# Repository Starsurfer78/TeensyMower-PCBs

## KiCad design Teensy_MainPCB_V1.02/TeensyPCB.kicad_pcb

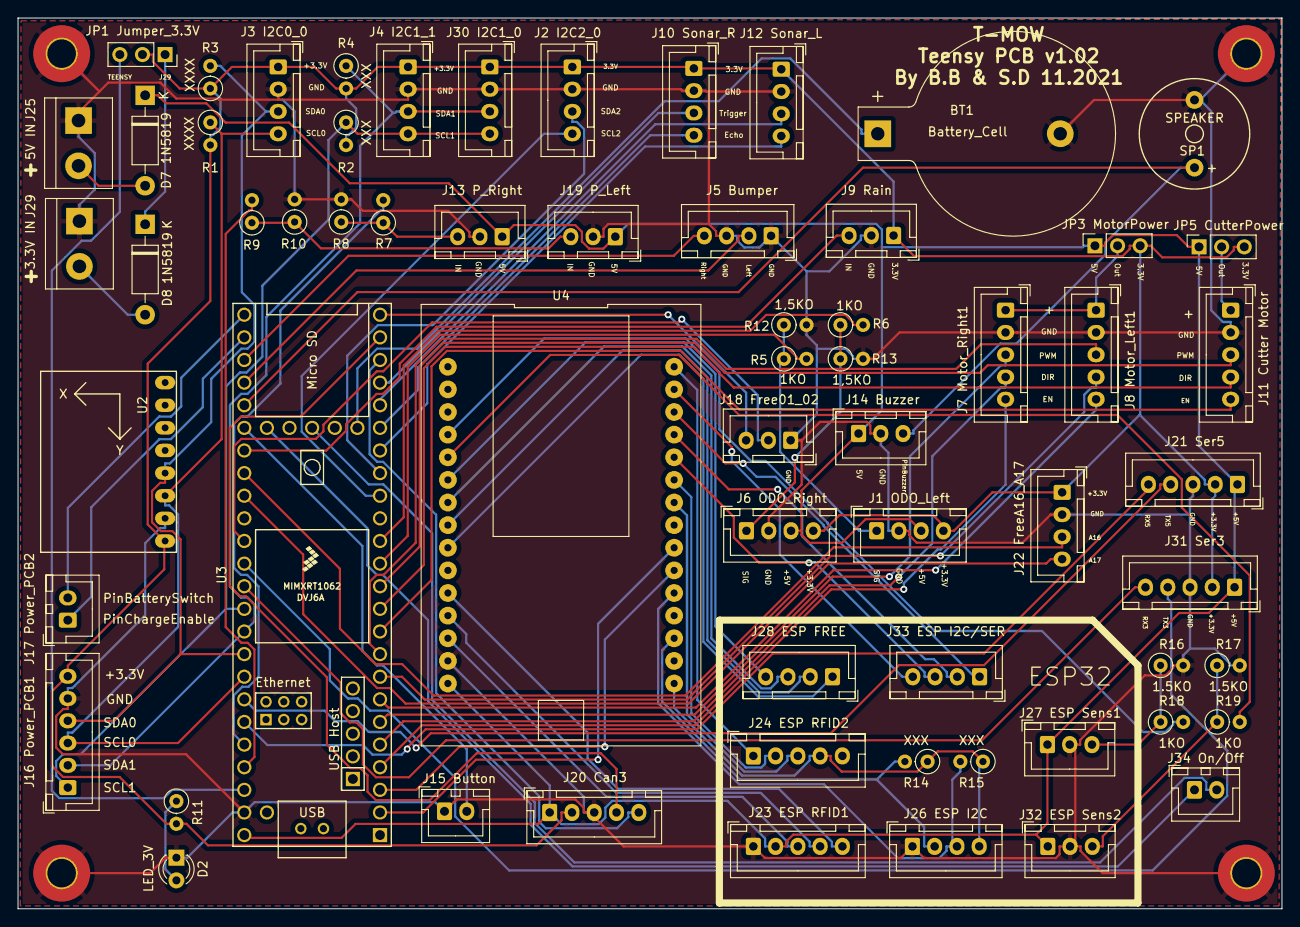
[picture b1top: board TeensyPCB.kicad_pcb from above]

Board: 2 copper layers, 141.9 x 100.0 mm, 68 parts (0 on the bottom side), 80 nets.

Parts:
BT1: Battery_Cell; BatteryHolder_Keystone_103_1x20mm
D2: LED_3V; LED_D3.0mm
D7, D8: 1N5819; D_DO-41_SOD81_P10.16mm_Horizontal
H1, H2, H3, H4: MountingHole_Pad; MountingHole_3.2mm_M3_Pad_TopBottom
J1 ODO_Left: ODO_Left; JST_XH_B4B-XH-A_1x04_P2.50mm_Vertical
J2 I2C2_0: I2C2_0; JST_XH_B4B-XH-A_1x04_P2.50mm_Vertical
J3 I2C0_0: I2C0_0; JST_XH_B4B-XH-A_1x04_P2.50mm_Vertical
J4 I2C1_1: I2C1_1; JST_XH_B4B-XH-A_1x04_P2.50mm_Vertical
J5 Bumper: Bumper; JST_XH_B4B-XH-A_1x04_P2.50mm_Vertical
J6 ODO_Right: ODO_Right; JST_XH_B4B-XH-A_1x04_P2.50mm_Vertical
J7 Motor_Right1: Motor_Right1; JST_XH_B5B-XH-A_1x05_P2.50mm_Vertical
J8 Motor_Left1: Motor_Left1; JST_XH_B5B-XH-A_1x05_P2.50mm_Vertical
J9 Rain: Rain; JST_XH_B3B-XH-A_1x03_P2.50mm_Vertical
J10 Sonar_R: Sonar_R; JST_XH_B4B-XH-A_1x04_P2.50mm_Vertical
J11 Cutter Motor: Cutter; JST_XH_B5B-XH-A_1x05_P2.50mm_Vertical
J12 Sonar_L: Sonar_L; JST_XH_B4B-XH-A_1x04_P2.50mm_Vertical
J13 P_Right: P_Right; JST_XH_B3B-XH-A_1x03_P2.50mm_Vertical
J14 Buzzer: Buzzer; JST_XH_B3B-XH-A_1x03_P2.50mm_Vertical
J15 Button: Button; JST_XH_B2B-XH-A_1x02_P2.50mm_Vertical
J16 Power_PCB1: Power_PCB1; JST_XH_B6B-XH-A_1x06_P2.50mm_Vertical
J17 Power_PCB2: Power_PCB2; JST_XH_B2B-XH-A_1x02_P2.50mm_Vertical
J18 Free01_02: Free01_02; JST_XH_B3B-XH-A_1x03_P2.50mm_Vertical
J19 P_Left: P_Left; JST_XH_B3B-XH-A_1x03_P2.50mm_Vertical
J20 Can3: Can3; JST_XH_B5B-XH-A_1x05_P2.50mm_Vertical
J21 Ser5: Ser5; JST_XH_B5B-XH-A_1x05_P2.50mm_Vertical
J22 FreeA16_A17: FreeA16_A17; JST_XH_B4B-XH-A_1x04_P2.50mm_Vertical
J23 ESP RFID1: ESP RFID1; JST_XH_B5B-XH-A_1x05_P2.50mm_Vertical
J24 ESP RFID2: ESP RFID2; JST_XH_B5B-XH-A_1x05_P2.50mm_Vertical
J25: 5V IN; TerminalBlock_bornier-2_P5.08mm
J26 ESP I2C: ESP32 I2C; JST_XH_B4B-XH-A_1x04_P2.50mm_Vertical
J27 ESP Sens1: ESP32 Sens1; JST_XH_B3B-XH-A_1x03_P2.50mm_Vertical
J28 ESP FREE: ESP32 FREE; JST_XH_B4B-XH-A_1x04_P2.50mm_Vertical
J29: 3.3V IN; TerminalBlock_bornier-2_P5.08mm
J30 I2C1_0: I2C1_0; JST_XH_B4B-XH-A_1x04_P2.50mm_Vertical
J31 Ser3: Ser3; JST_XH_B5B-XH-A_1x05_P2.50mm_Vertical
J32 ESP Sens2: ESP32 Sens2; JST_XH_B3B-XH-A_1x03_P2.50mm_Vertical
J33 ESP I2C/SER: ESP32 I2C/SER; JST_XH_B4B-XH-A_1x04_P2.50mm_Vertical
J34 On/Off: Teensy On/Off; JST_XH_B2B-XH-A_1x02_P2.50mm_Vertical
JP1 Jumper_3.3V: Jumper_3.3V; PinSocket_1x03_P2.54mm_Vertical
JP3 MotorPower: MotorPower; PinSocket_1x03_P2.54mm_Vertical
JP5 CutterPower: CutterPower; PinSocket_1x03_P2.54mm_Vertical
R1, R3: XXXX; R_Axial_DIN0207_L6.3mm_D2.5mm_P2.54mm_Vertical
R2, R4, R14, R15: XXX; R_Axial_DIN0207_L6.3mm_D2.5mm_P2.54mm_Vertical
R5, R6, R7, R9, R18, R19: 1KO; R_Axial_DIN0207_L6.3mm_D2.5mm_P2.54mm_Vertical
R8, R10, R16, R17: 1.5KO; R_Axial_DIN0207_L6.3mm_D2.5mm_P2.54mm_Vertical
R11: 100; R_Axial_DIN0207_L6.3mm_D2.5mm_P2.54mm_Vertical
R12, R13: 1,5KO; R_Axial_DIN0207_L6.3mm_D2.5mm_P2.54mm_Vertical
SP1: SPEAKER; Buzzer_12x9.5RM7.6
U2: GY-521
U3: Teensy4.1; Teensy41
U4: ESP32-DEVKIT-V1

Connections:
+3V3: J1 ODO_Left.4, J2 I2C2_0.1, J3 I2C0_0.1, J4 I2C1_1.1, J6 ODO_Right.4, J9 Rain.1, J10 Sonar_R.1, J12 Sonar_L.1, J16 Power_PCB1.6, J20 Can3.2, J21 Ser5.2, J22 FreeA16_A17.1, J30 I2C1_0.1, J31 Ser3.2, JP1 Jumper_3.3V.2, JP3 MotorPower.3, JP5 CutterPower.3, R1.2, R2.2, R3.1, R4.2, R11.2, U2.1
+5V: D7.1, J1 ODO_Left.3, J6 ODO_Right.3, J13 P_Right.1, J14 Buzzer.1, J19 P_Left.1, J20 Can3.1, J21 Ser5.1, J23 ESP RFID1.2, J27 ESP Sens1.1, J31 Ser3.1, J32 ESP Sens2.1, JP3 MotorPower.1, JP5 CutterPower.1, U3.48, U4.15
CRX3: J20 Can3.5, U3.22
CTX3: J20 Can3.4, U3.23
Free01: J18 Free01_02.2, U3.35
Free02: J18 Free01_02.3, U3.24
FreeA16: J22 FreeA16_A17.3, U3.32
FreeA17: J22 FreeA16_A17.4, U3.33
GND: BT1.2, D2.1, H1.1, H2.1, H3.1, H4.1, J1 ODO_Left.2, J2 I2C2_0.2, J3 I2C0_0.2, J4 I2C1_1.2, J5 Bumper.1, J5 Bumper.3, J6 ODO_Right.2, J7 Motor_Right1.2, J8 Motor_Left1.2, J9 Rain.2, J10 Sonar_R.2, J11 Cutter Motor.2, J12 Sonar_L.2, J13 P_Right.2, J14 Buzzer.2, J15 Button.1, J16 Power_PCB1.5, J18 Free01_02.1, J19 P_Left.2, J20 Can3.3, J21 Ser5.3, J22 FreeA16_A17.2, J23 ESP RFID1.1, J25.1, J26 ESP I2C.1, J27 ESP Sens1.2, J29.1, J30 I2C1_0.2, J31 Ser3.3, J32 ESP Sens2.2, R8.2, R10.2, R12.2, R13.2, R16.2, R17.2, SP1.1, U2.2, U3.47, U4.14
unnamed: BT1.1, U3.50
unnamed: D2.2, R11.1
unnamed: D7.2, J25.2
unnamed: D8.1, JP1 Jumper_3.3V.1
unnamed: D8.2, J29.2
unnamed: J1 ODO_Left.1, R5.1, R12.1
unnamed: J6 ODO_Right.1, R6.1, R13.1
unnamed: J7 Motor_Right1.1, J8 Motor_Left1.1, JP3 MotorPower.2
unnamed: J11 Cutter Motor.1, JP5 CutterPower.2
unnamed: J13 P_Right.3, R7.1, R8.1
unnamed: J19 P_Left.3, R9.1, R10.1
unnamed: J23 ESP RFID1.3, U4.13
unnamed: J23 ESP RFID1.4, U4.12
unnamed: J23 ESP RFID1.5, U4.11
unnamed: J24 ESP RFID2.1, U4.30
unnamed: J24 ESP RFID2.2, U4.25
unnamed: J24 ESP RFID2.3, U4.24
unnamed: J24 ESP RFID2.4, J26 ESP I2C.4, R14.1, R15.1, U4.16
unnamed: J26 ESP I2C.2, R14.2, U4.18
unnamed: J26 ESP I2C.3, R15.2, U4.20
unnamed: J27 ESP Sens1.3, R16.1, R18.1
unnamed: J28 ESP FREE.1, U4.9
unnamed: J28 ESP FREE.2, U4.8
unnamed: J28 ESP FREE.3, U4.7
unnamed: J28 ESP FREE.4, U4.6
unnamed: J32 ESP Sens2.3, R17.1, R19.1
unnamed: J33 ESP I2C/SER.1, U4.28
unnamed: J33 ESP I2C/SER.2, U4.27
unnamed: J33 ESP I2C/SER.3, U4.26
unnamed: J33 ESP I2C/SER.4, U4.29
unnamed: J34 On/Off.1, U3.54
unnamed: J34 On/Off.2, U3.52
unnamed: JP1 Jumper_3.3V.3, U3.46
unnamed: R18.2, U4.4
unnamed: R19.2, U4.5
RX1: U3.2, U4.22
RX3: J31 Ser3.5, U3.37
RX5: J21 Ser5.5, U3.43
SCL0: J3 I2C0_0.4, J16 Power_PCB1.3, R1.1, U2.3, U3.41
SCL1: J4 I2C1_1.4, J16 Power_PCB1.1, J30 I2C1_0.4, R2.1, U3.38
SCL2: J2 I2C2_0.4, U3.16
SDA0: J3 I2C0_0.3, J16 Power_PCB1.4, R3.2, U2.4, U3.40
SDA1: J4 I2C1_1.3, J16 Power_PCB1.2, J30 I2C1_0.3, R4.1, U3.39
SDA2: J2 I2C2_0.3, U3.17
TX1: U3.3, U4.21
TX3: J31 Ser3.4, U3.36
TX5: J21 Ser5.4, U3.42
pinBatterySwitch: J17 Power_PCB2.2, U3.25
pinBumperLeft: J5 Bumper.4, U3.27
pinBumperRight: J5 Bumper.2, U3.28
pinButton: J15 Button.2, U3.30
pinBuzzer: J14 Buzzer.3, SP1.2, U3.29
pinChargeEnable: J17 Power_PCB2.1, U3.26
pinMotorLeftDir: J8 Motor_Left1.4, U3.8
pinMotorLeftEnable: J8 Motor_Left1.5, U3.7
pinMotorLeftPWM: J8 Motor_Left1.3, U3.9
pinMotorMowDir: J11 Cutter Motor.4, U3.11
pinMotorMowEnable: J11 Cutter Motor.5, U3.10
pinMotorMowPWM: J11 Cutter Motor.3, U3.12
pinMotorRightDir: J7 Motor_Right1.4, U3.5
pinMotorRightEnable: J7 Motor_Right1.5, U3.4
pinMotorRightPWM: J7 Motor_Right1.3, U3.6
pinOdometryLeft: R6.2, U3.14
pinOdometryRight: R5.2, U3.13
pinPerimeterLeft: R9.2, U3.45
pinPerimeterRight: R7.2, U3.44
pinRain: J9 Rain.3, U3.31
pinSonarLeftEcho: J12 Sonar_L.4, U3.18
pinSonarLeftTrigger: J12 Sonar_L.3, U3.20
pinSonarRightEcho: J10 Sonar_R.4, U3.19
pinSonarRightTrigger: J10 Sonar_R.3, U3.21
